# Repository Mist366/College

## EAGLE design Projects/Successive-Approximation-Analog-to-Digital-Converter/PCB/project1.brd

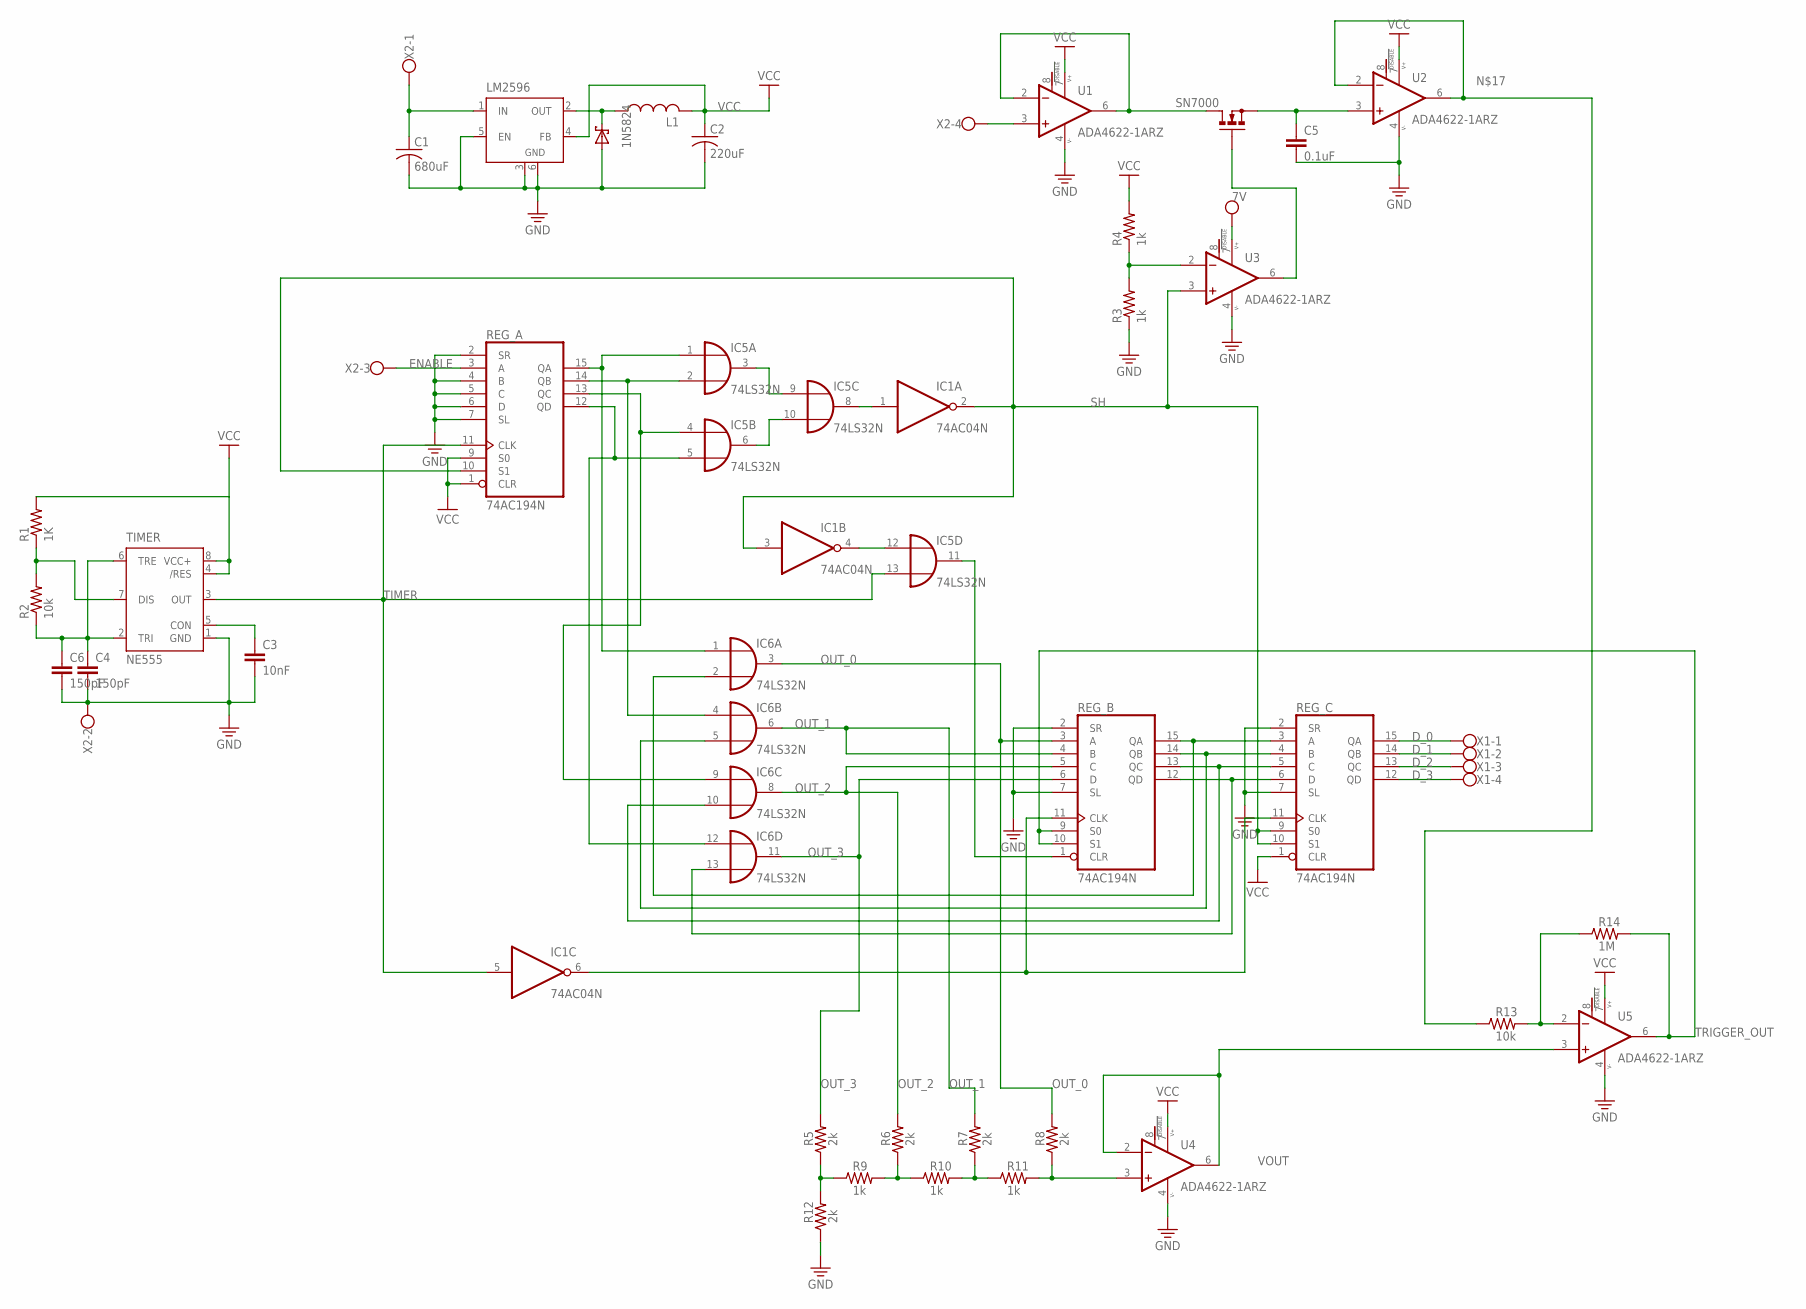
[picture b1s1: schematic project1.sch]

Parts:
1N5824: SCHOTTKY-DIODECB417-15; CB417-15
C1: 680uF; C025-024X044
C2: 220uF; C025-024X044
C3: 10nF; C050-024X044
C4, C6: 150pF; C050-024X044
C5: 0.1uF; C050-024X044
IC1: 74AC04N; DIL14
IC5, IC6: 74LS32N; DIL14
L1: L-US0204/7; 0204/7
LM2596: LM2596S; TO263-5
R1: 1K; 0204/7
R2, R13: 10k; 0204/7
R3, R4, R9, R10, R11: 1k; 0204/7
R5, R6, R7, R8, R12: 2k; 0204/7
R14: 1M; 0204/7
REG_A: 74AC194N; DIL16
REG_B: 74AC194N; DIL16
REG_C: 74AC194N; DIL16
SN7000: BS170; SOT54E
TIMER: NE555; DIL-08
U1, U2, U3, U4, U5: ADA4622-1ARZ; SOIC127P600X175-8N
X1, X2: W237-4

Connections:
D_0: REG_C.15 (QA), X1.1
D_1: REG_C.14 (QB), X1.2
D_2: REG_C.13 (QC), X1.3
D_3: REG_C.12 (QD), X1.4
ENABLE: REG_A.3 (A), X2.3
GND: 1N5824.A, C1.2, C2.2, C3.2, C4.2, C5.2, C6.2, IC1.7 (GND), IC5.7 (GND), IC6.7 (GND), LM2596.3 (GND), LM2596.5 (EN), LM2596.6 (GND), R3.1, R12.1, REG_A.2 (SR), REG_A.4 (B), REG_A.5 (C), REG_A.6 (D), REG_A.7 (SL), REG_A.8 (GND), REG_B.2 (SR), REG_B.7 (SL), REG_B.8 (GND), REG_C.2 (SR), REG_C.7 (SL), REG_C.8 (GND), TIMER.1 (GND), U1.4 (V-), U2.4 (V-), U3.4 (V-), U4.4 (V-), U5.4 (V-), X2.2
unnamed: IC5.1 (I0), IC6.1 (I0), REG_A.15 (QA)
unnamed: IC5.2 (I1), IC6.4 (I0), REG_A.14 (QB)
unnamed: IC5.4 (I0), IC6.9 (I0), REG_A.13 (QC)
unnamed: IC5.5 (I1), IC6.12 (I0), REG_A.12 (QD)
unnamed: IC5.6 (O), IC5.10 (I1)
unnamed: IC5.3 (O), IC5.9 (I0)
unnamed: IC1.1 (I), IC5.8 (O)
unnamed: IC1.4 (O), IC5.12 (I0)
unnamed: C3.1, TIMER.5 (CON)
unnamed: IC5.11 (O), REG_B.1 (CLR)
unnamed: R1.1, R2.2, TIMER.7 (DIS)
unnamed: C4.1, C6.1, R2.1, TIMER.2 (TRI), TIMER.6 (TRE)
unnamed: R13.1, U2.2 (-IN), U2.6 (OUT)
unnamed: IC1.6 (O), REG_B.11 (CLK), REG_C.11 (CLK)
unnamed: 1N5824.C, L1.1, LM2596.2 (OUT)
unnamed: SN7000.D, U1.2 (-IN), U1.6 (OUT)
unnamed: R3.2, R4.1, U3.2 (-IN)
unnamed: R6.1, R9.2, R10.1
unnamed: C5.1, SN7000.S, U2.3 (+IN)
unnamed: SN7000.G, U3.6 (OUT)
unnamed: R7.1, R10.2, R11.1
unnamed: R5.1, R9.1, R12.2
unnamed: R8.1, R11.2, U4.3 (+IN)
unnamed: R13.2, R14.1, U5.2 (-IN)
O0: IC6.2 (I1), REG_B.15 (QA), REG_C.3 (A)
O1: IC6.5 (I1), REG_B.14 (QB), REG_C.4 (B)
O2: IC6.10 (I1), REG_B.13 (QC), REG_C.5 (C)
O3: IC6.13 (I1), REG_B.12 (QD), REG_C.6 (D)
OUT_0: IC6.3 (O), R8.2, REG_B.3 (A)
OUT_1: IC6.6 (O), R7.2, REG_B.4 (B)
OUT_2: IC6.8 (O), R6.2, REG_B.5 (C)
OUT_3: IC6.11 (O), R5.2, REG_B.6 (D)
SH: IC1.2 (O), IC1.3 (I), REG_A.10 (S1), REG_C.9 (S0), REG_C.10 (S1), U3.3 (+IN)
TIMER: IC1.5 (I), IC5.13 (I1), REG_A.11 (CLK), TIMER.3 (OUT)
TRIGGER_OUT: R14.2, REG_B.9 (S0), REG_B.10 (S1), U5.6 (OUT)
VCC: C2.1, IC1.14 (VCC), IC5.14 (VCC), IC6.14 (VCC), L1.2, LM2596.4 (FB), R1.2, R4.2, REG_A.1 (CLR), REG_A.9 (S0), REG_A.16 (VCC), REG_B.16 (VCC), REG_C.1 (CLR), REG_C.16 (VCC), TIMER.4 (/RES), TIMER.8 (VCC+), U1.7 (V+), U2.7 (V+), U3.7 (V+), U4.7 (V+), U5.7 (V+)
VIN: C1.1, LM2596.1 (IN), X2.1
VOUT: U4.2 (-IN), U4.6 (OUT), U5.3 (+IN)
V_IN: U1.3 (+IN), X2.4

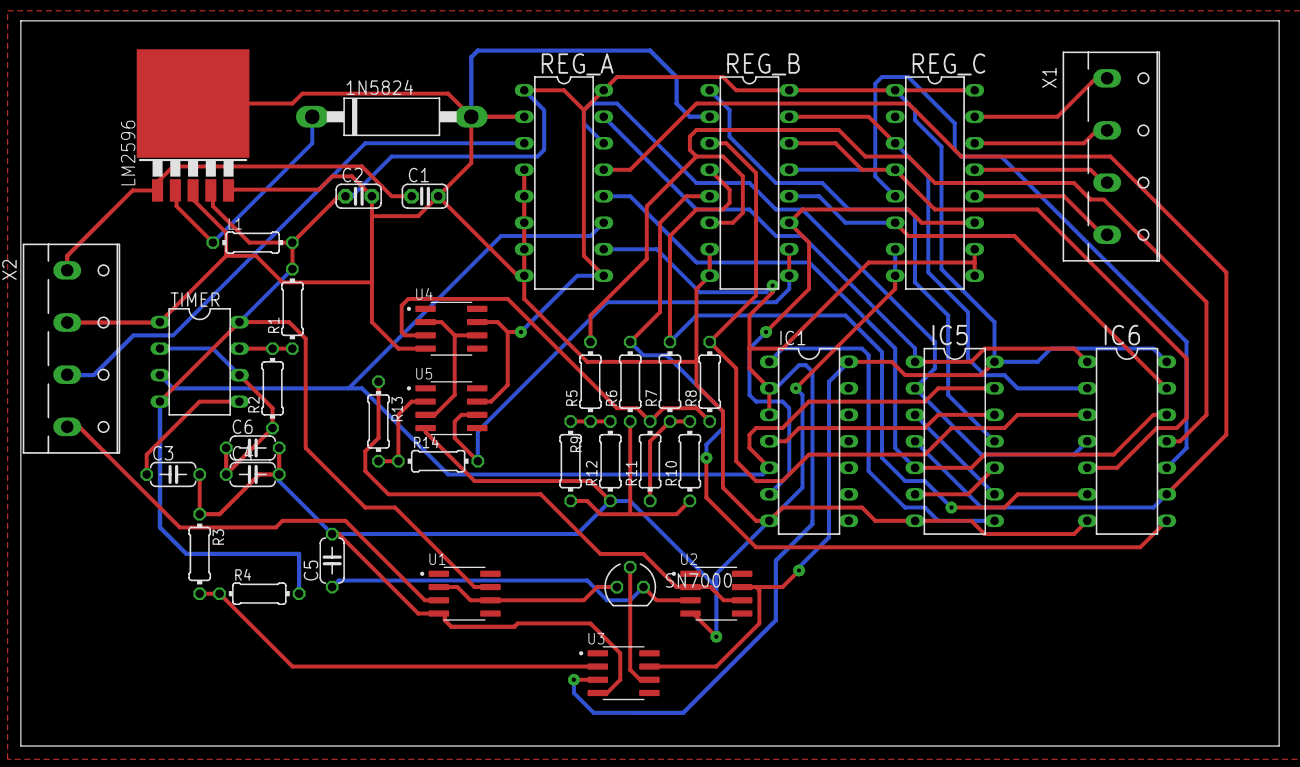
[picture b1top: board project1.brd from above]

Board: 2 copper layers, 120.6 x 69.5 mm, 38 parts (0 on the bottom side), 45 nets.

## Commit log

2021-06-20 Reformatting
2021-06-20 Add Formula One Display Project
2021-12-06 Adding MLP Project
2022-05-11 Reformatting and AI-Foosball Addition
2022-05-11 Created AI-Fooball
2022-10-06 Add files via upload
    Add PDF of project 2 report
